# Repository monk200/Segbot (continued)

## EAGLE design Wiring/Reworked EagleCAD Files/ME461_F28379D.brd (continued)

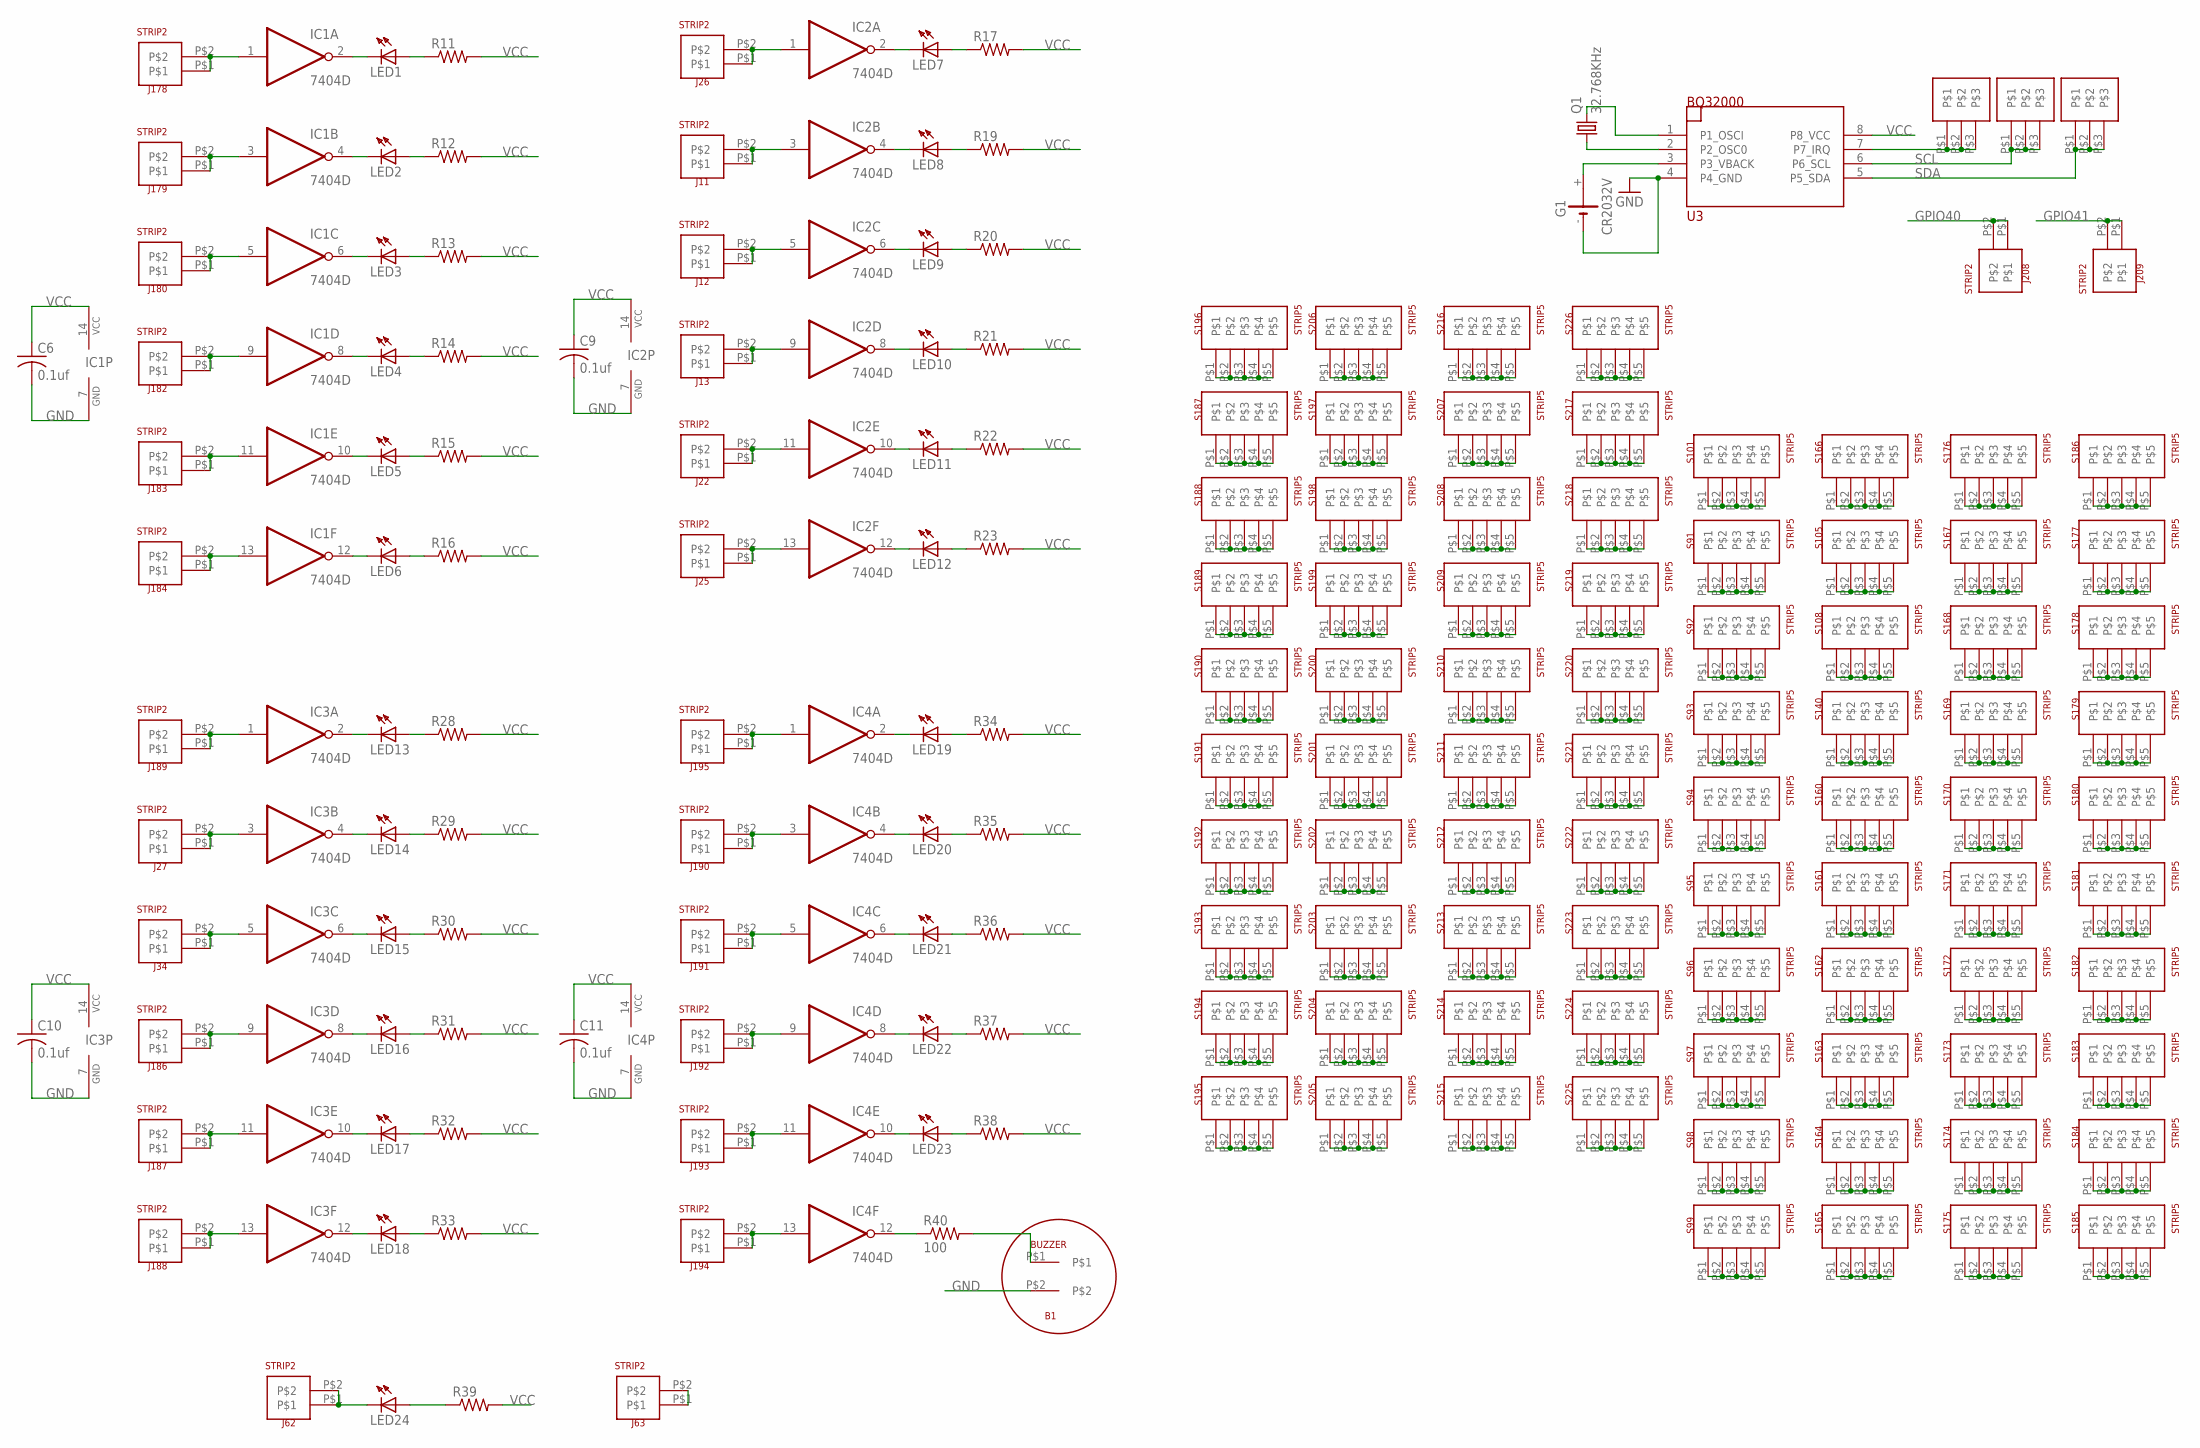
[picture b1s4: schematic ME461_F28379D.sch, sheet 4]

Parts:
B1: BUZZER
C6, C9, C10, C11: 0.1uf; C1206
G1: CR2032V
IC1, IC2, IC3, IC4: 7404D; SO14
J1, J2, J3: STRIP3
J11, J12, J13, J22, J25, J26, J27, J34, J62, J63, J178, J179, J180, J182, J183, J184, J186, J187, J188, J189, J190, J191, J192, J193, J194, J195, J208, J209: STRIP2
LED1, LED2, LED3, LED4, LED5, LED6, LED7, LED8, LED9, LED10, LED11, LED12, LED13, LED14, LED15, LED16, LED17, LED18, LED19, LED20, LED21, LED22, LED23, LED24: LED3MM
Q1: 32.768KHz; TC26H
R11, R12, R13, R14, R15, R16, R17, R19, R20, R21, R22, R23, R28, R29, R30, R31, R32, R33, R34, R35, R36, R37, R38, R39: R-US_R1206; R1206
R40: 100; R1206
S91, S92, S93, S94, S95, S96, S97, S98, S99, S101, S105, S108, S140, S160, S161, S162, S163, S164, S165, S166, S167, S168, S169, S170, S171, S172, S173, S174, S175, S176, S177, S178, S179, S180, S181, S182, S183, S184, S185, S186, S187, S188, S189, S190, S191, S192, S193, S194, S195, S196, S197, S198, S199, S200, S201, S202, S203, S204, S205, S206, S207, S208, S209, S210, S211, S212, S213, S214, S215, S216, S217, S218, S219, S220, S221, S222, S223, S224, S225, S226: STRIP5
U3: BQ32000; SO08

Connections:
GND: B1.P$2, C6.2, C9.2, C10.2, C11.2, G1.-, IC1.7 (GND), IC2.7 (GND), IC3.7 (GND), IC4.7 (GND), U3.4 (P4_GND); also elsewhere on the board
GPIO40: J208.P$1, J208.P$2; also elsewhere on the board
GPIO41: J209.P$1, J209.P$2; also elsewhere on the board
unnamed: J62.P$1, J62.P$2, LED24.K (C)
unnamed: IC4.12 (O), R40.1
unnamed: B1.P$1, R40.2
unnamed: Q1.1, U3.2 (P2_OSC0)
unnamed: J63.P$1, J63.P$2
unnamed: Q1.2, U3.1 (P1_OSCI)
unnamed: J1.P$1, J1.P$2, J1.P$3, U3.7 (P7_IRQ)
unnamed: G1.+, U3.3 (P3_VBACK)
unnamed: IC2.1 (I), J26.P$1, J26.P$2
unnamed: IC2.2 (O), LED7.K (C)
unnamed: LED7.A, R17.1
unnamed: IC2.3 (I), J11.P$1, J11.P$2
unnamed: IC2.4 (O), LED8.K (C)
unnamed: LED8.A, R19.1
unnamed: IC2.5 (I), J12.P$1, J12.P$2
unnamed: IC2.6 (O), LED9.K (C)
unnamed: S91.P$1, S91.P$2, S91.P$3, S91.P$4, S91.P$5
unnamed: S92.P$1, S92.P$2, S92.P$3, S92.P$4, S92.P$5
unnamed: S93.P$1, S93.P$2, S93.P$3, S93.P$4, S93.P$5
unnamed: S94.P$1, S94.P$2, S94.P$3, S94.P$4, S94.P$5
unnamed: S95.P$1, S95.P$2, S95.P$3, S95.P$4, S95.P$5
unnamed: S96.P$1, S96.P$2, S96.P$3, S96.P$4, S96.P$5
unnamed: S97.P$1, S97.P$2, S97.P$3, S97.P$4, S97.P$5
unnamed: S98.P$1, S98.P$2, S98.P$3, S98.P$4, S98.P$5
unnamed: S99.P$1, S99.P$2, S99.P$3, S99.P$4, S99.P$5
unnamed: S101.P$1, S101.P$2, S101.P$3, S101.P$4, S101.P$5
unnamed: S105.P$1, S105.P$2, S105.P$3, S105.P$4, S105.P$5
unnamed: S108.P$1, S108.P$2, S108.P$3, S108.P$4, S108.P$5
unnamed: S140.P$1, S140.P$2, S140.P$3, S140.P$4, S140.P$5
unnamed: S160.P$1, S160.P$2, S160.P$3, S160.P$4, S160.P$5
unnamed: S161.P$1, S161.P$2, S161.P$3, S161.P$4, S161.P$5
unnamed: S162.P$1, S162.P$2, S162.P$3, S162.P$4, S162.P$5
unnamed: S163.P$1, S163.P$2, S163.P$3, S163.P$4, S163.P$5
unnamed: S164.P$1, S164.P$2, S164.P$3, S164.P$4, S164.P$5
unnamed: S165.P$1, S165.P$2, S165.P$3, S165.P$4, S165.P$5
unnamed: S166.P$1, S166.P$2, S166.P$3, S166.P$4, S166.P$5
unnamed: S167.P$1, S167.P$2, S167.P$3, S167.P$4, S167.P$5
unnamed: S168.P$1, S168.P$2, S168.P$3, S168.P$4, S168.P$5
unnamed: S169.P$1, S169.P$2, S169.P$3, S169.P$4, S169.P$5
unnamed: S170.P$1, S170.P$2, S170.P$3, S170.P$4, S170.P$5
unnamed: S171.P$1, S171.P$2, S171.P$3, S171.P$4, S171.P$5
unnamed: S172.P$1, S172.P$2, S172.P$3, S172.P$4, S172.P$5
unnamed: S173.P$1, S173.P$2, S173.P$3, S173.P$4, S173.P$5
unnamed: S174.P$1, S174.P$2, S174.P$3, S174.P$4, S174.P$5
unnamed: S175.P$1, S175.P$2, S175.P$3, S175.P$4, S175.P$5
unnamed: S176.P$1, S176.P$2, S176.P$3, S176.P$4, S176.P$5
unnamed: S177.P$1, S177.P$2, S177.P$3, S177.P$4, S177.P$5
unnamed: S178.P$1, S178.P$2, S178.P$3, S178.P$4, S178.P$5
unnamed: S179.P$1, S179.P$2, S179.P$3, S179.P$4, S179.P$5
unnamed: S180.P$1, S180.P$2, S180.P$3, S180.P$4, S180.P$5
unnamed: S181.P$1, S181.P$2, S181.P$3, S181.P$4, S181.P$5
unnamed: S182.P$1, S182.P$2, S182.P$3, S182.P$4, S182.P$5
unnamed: S183.P$1, S183.P$2, S183.P$3, S183.P$4, S183.P$5
unnamed: S184.P$1, S184.P$2, S184.P$3, S184.P$4, S184.P$5
unnamed: S185.P$1, S185.P$2, S185.P$3, S185.P$4, S185.P$5
unnamed: S186.P$1, S186.P$2, S186.P$3, S186.P$4, S186.P$5
unnamed: S187.P$1, S187.P$2, S187.P$3, S187.P$4, S187.P$5
unnamed: S188.P$1, S188.P$2, S188.P$3, S188.P$4, S188.P$5
unnamed: S189.P$1, S189.P$2, S189.P$3, S189.P$4, S189.P$5
unnamed: S190.P$1, S190.P$2, S190.P$3, S190.P$4, S190.P$5
unnamed: S191.P$1, S191.P$2, S191.P$3, S191.P$4, S191.P$5
unnamed: S192.P$1, S192.P$2, S192.P$3, S192.P$4, S192.P$5
unnamed: S193.P$1, S193.P$2, S193.P$3, S193.P$4, S193.P$5
unnamed: S194.P$1, S194.P$2, S194.P$3, S194.P$4, S194.P$5
unnamed: S195.P$1, S195.P$2, S195.P$3, S195.P$4, S195.P$5
unnamed: S196.P$1, S196.P$2, S196.P$3, S196.P$4, S196.P$5
unnamed: S197.P$1, S197.P$2, S197.P$3, S197.P$4, S197.P$5
unnamed: S198.P$1, S198.P$2, S198.P$3, S198.P$4, S198.P$5
unnamed: S199.P$1, S199.P$2, S199.P$3, S199.P$4, S199.P$5
unnamed: S200.P$1, S200.P$2, S200.P$3, S200.P$4, S200.P$5
unnamed: S201.P$1, S201.P$2, S201.P$3, S201.P$4, S201.P$5
unnamed: S202.P$1, S202.P$2, S202.P$3, S202.P$4, S202.P$5
unnamed: S203.P$1, S203.P$2, S203.P$3, S203.P$4, S203.P$5
unnamed: S204.P$1, S204.P$2, S204.P$3, S204.P$4, S204.P$5
unnamed: S205.P$1, S205.P$2, S205.P$3, S205.P$4, S205.P$5
unnamed: S206.P$1, S206.P$2, S206.P$3, S206.P$4, S206.P$5
unnamed: S207.P$1, S207.P$2, S207.P$3, S207.P$4, S207.P$5
unnamed: S208.P$1, S208.P$2, S208.P$3, S208.P$4, S208.P$5
unnamed: S209.P$1, S209.P$2, S209.P$3, S209.P$4, S209.P$5
unnamed: S210.P$1, S210.P$2, S210.P$3, S210.P$4, S210.P$5
unnamed: S211.P$1, S211.P$2, S211.P$3, S211.P$4, S211.P$5
unnamed: S212.P$1, S212.P$2, S212.P$3, S212.P$4, S212.P$5
unnamed: S213.P$1, S213.P$2, S213.P$3, S213.P$4, S213.P$5
unnamed: S214.P$1, S214.P$2, S214.P$3, S214.P$4, S214.P$5
unnamed: S215.P$1, S215.P$2, S215.P$3, S215.P$4, S215.P$5
unnamed: S216.P$1, S216.P$2, S216.P$3, S216.P$4, S216.P$5
unnamed: S217.P$1, S217.P$2, S217.P$3, S217.P$4, S217.P$5
unnamed: S218.P$1, S218.P$2, S218.P$3, S218.P$4, S218.P$5
unnamed: S219.P$1, S219.P$2, S219.P$3, S219.P$4, S219.P$5
unnamed: S220.P$1, S220.P$2, S220.P$3, S220.P$4, S220.P$5
unnamed: S221.P$1, S221.P$2, S221.P$3, S221.P$4, S221.P$5
unnamed: S222.P$1, S222.P$2, S222.P$3, S222.P$4, S222.P$5
unnamed: S223.P$1, S223.P$2, S223.P$3, S223.P$4, S223.P$5
unnamed: S224.P$1, S224.P$2, S224.P$3, S224.P$4, S224.P$5
unnamed: S225.P$1, S225.P$2, S225.P$3, S225.P$4, S225.P$5
unnamed: S226.P$1, S226.P$2, S226.P$3, S226.P$4, S226.P$5
unnamed: IC1.1 (I), J178.P$1, J178.P$2
unnamed: IC1.2 (O), LED1.K (C)
unnamed: LED1.A, R11.1
unnamed: IC1.3 (I), J179.P$1, J179.P$2
unnamed: IC1.4 (O), LED2.K (C)
unnamed: LED2.A, R12.1
unnamed: IC1.5 (I), J180.P$1, J180.P$2
unnamed: IC1.6 (O), LED3.K (C)
unnamed: LED3.A, R13.1
unnamed: IC1.9 (I), J182.P$1, J182.P$2
unnamed: IC1.8 (O), LED4.K (C)
unnamed: LED4.A, R14.1
unnamed: IC1.11 (I), J183.P$1, J183.P$2
unnamed: IC1.10 (O), LED5.K (C)
unnamed: LED5.A, R15.1
unnamed: IC1.13 (I), J184.P$1, J184.P$2
unnamed: IC1.12 (O), LED6.K (C)
unnamed: LED6.A, R16.1
unnamed: LED9.A, R20.1
unnamed: IC2.9 (I), J13.P$1, J13.P$2
unnamed: IC2.8 (O), LED10.K (C)
unnamed: LED10.A, R21.1
unnamed: IC2.11 (I), J22.P$1, J22.P$2
unnamed: IC2.10 (O), LED11.K (C)
unnamed: LED11.A, R22.1
unnamed: IC2.13 (I), J25.P$1, J25.P$2
unnamed: IC2.12 (O), LED12.K (C)
unnamed: LED12.A, R23.1
unnamed: IC3.1 (I), J189.P$1, J189.P$2
unnamed: IC3.2 (O), LED13.K (C)
unnamed: LED13.A, R28.1
unnamed: IC3.3 (I), J27.P$1, J27.P$2
unnamed: IC3.4 (O), LED14.K (C)
unnamed: LED14.A, R29.1
unnamed: IC3.5 (I), J34.P$1, J34.P$2
unnamed: IC3.6 (O), LED15.K (C)
unnamed: LED15.A, R30.1
unnamed: IC3.9 (I), J186.P$1, J186.P$2
unnamed: IC3.8 (O), LED16.K (C)
unnamed: LED16.A, R31.1
unnamed: IC3.11 (I), J187.P$1, J187.P$2
unnamed: IC3.10 (O), LED17.K (C)
unnamed: LED17.A, R32.1
unnamed: IC3.13 (I), J188.P$1, J188.P$2
unnamed: IC3.12 (O), LED18.K (C)
unnamed: LED18.A, R33.1
unnamed: IC4.1 (I), J195.P$1, J195.P$2
unnamed: IC4.2 (O), LED19.K (C)
unnamed: LED19.A, R34.1
unnamed: IC4.3 (I), J190.P$1, J190.P$2
unnamed: IC4.4 (O), LED20.K (C)
unnamed: LED20.A, R35.1
unnamed: IC4.5 (I), J191.P$1, J191.P$2
unnamed: IC4.6 (O), LED21.K (C)
unnamed: LED21.A, R36.1
unnamed: IC4.9 (I), J192.P$1, J192.P$2
unnamed: IC4.8 (O), LED22.K (C)
unnamed: LED22.A, R37.1
unnamed: IC4.11 (I), J193.P$1, J193.P$2
unnamed: IC4.10 (O), LED23.K (C)
unnamed: LED23.A, R38.1
unnamed: IC4.13 (I), J194.P$1, J194.P$2
unnamed: LED24.A, R39.1
SCL: J2.P$1, J2.P$2, J2.P$3, U3.6 (P6_SCL)
SDA: J3.P$1, J3.P$2, J3.P$3, U3.5 (P5_SDA)
VCC: C6.1, C9.1, C10.1, C11.1, IC1.14 (VCC), IC2.14 (VCC), IC3.14 (VCC), IC4.14 (VCC), R11.2, R12.2, R13.2, R14.2, R15.2, R16.2, R17.2, R19.2, R20.2, R21.2, R22.2, R23.2, R28.2, R29.2, R30.2, R31.2, R32.2, R33.2, R34.2, R35.2, R36.2, R37.2, R38.2, R39.2, U3.8 (P8_VCC); also elsewhere on the board

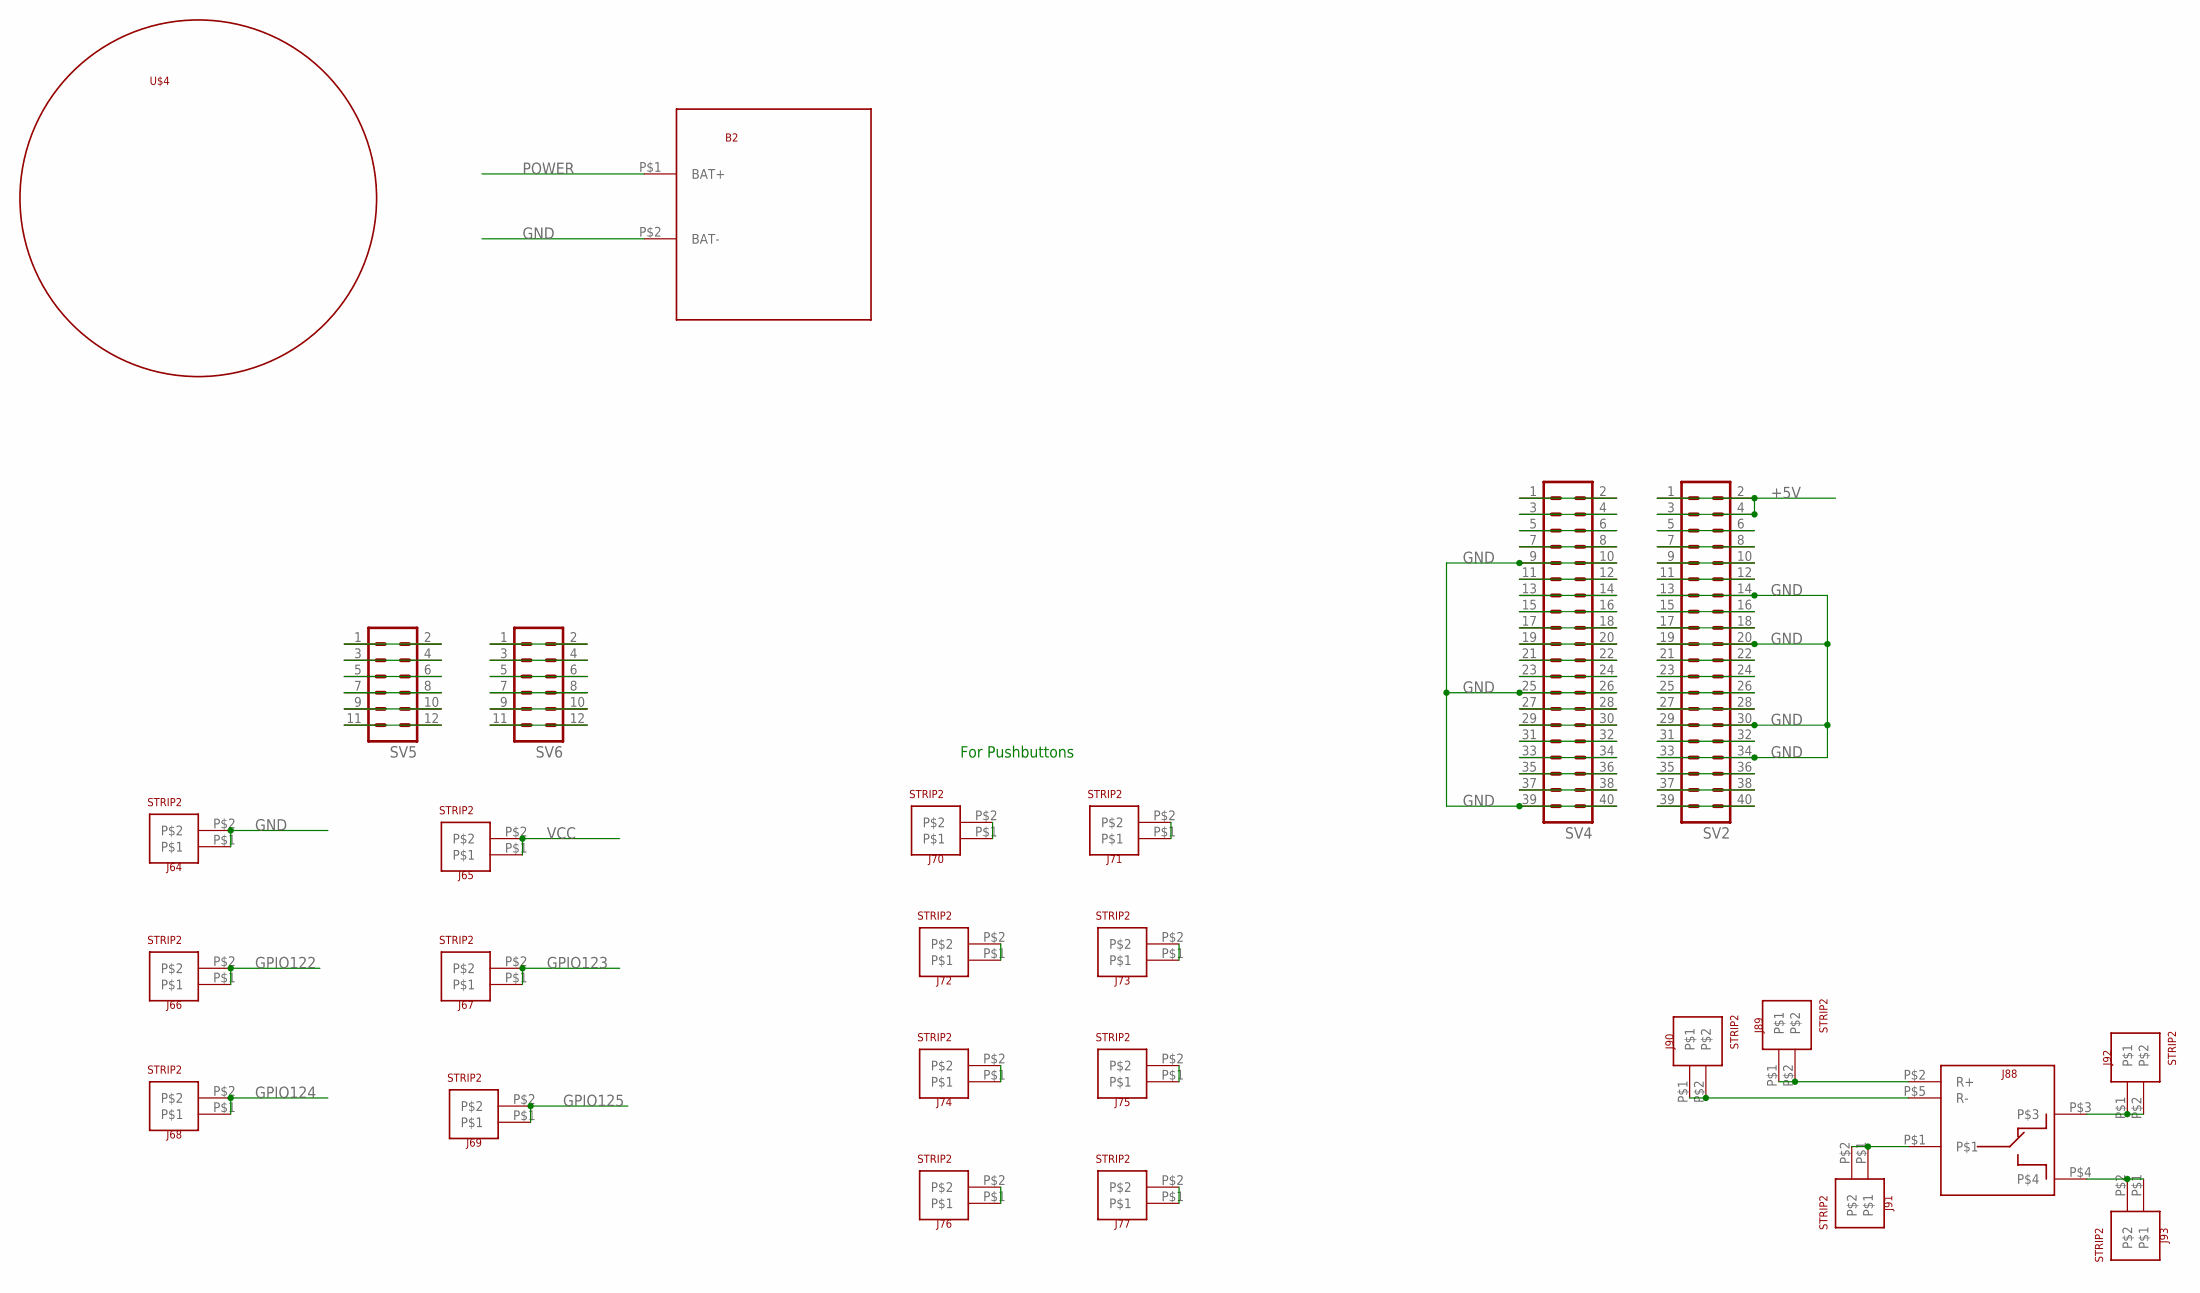
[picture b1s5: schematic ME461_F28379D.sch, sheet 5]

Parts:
B2: BATTERY_4AA_HOLDER
J64, J65, J66, J67, J68, J69, J70, J71, J72, J73, J74, J75, J76, J77, J89, J90, J91, J92, J93: STRIP2
J88: RELAY_JQC-3F_5V
SV2, SV4: MA20-2
SV5, SV6: MA06-2
U$4: CASTERWHEEL

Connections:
+5V: SV2.1, SV2.2, SV2.3, SV2.4; also elsewhere on the board
GND: B2.P$2 (BAT-), J64.P$1, J64.P$2, SV2.13, SV2.14, SV2.19, SV2.20, SV2.29, SV2.30, SV2.33, SV2.34, SV4.9, SV4.10, SV4.25, SV4.26, SV4.39, SV4.40; also elsewhere on the board
GPIO122: J66.P$1, J66.P$2; also elsewhere on the board
GPIO123: J67.P$1, J67.P$2; also elsewhere on the board
GPIO124: J68.P$1, J68.P$2; also elsewhere on the board
GPIO125: J69.P$1, J69.P$2; also elsewhere on the board
unnamed: SV4.1, SV4.2
unnamed: SV5.1, SV5.2
unnamed: SV5.3, SV5.4
unnamed: SV5.5, SV5.6
unnamed: SV4.3, SV4.4
unnamed: SV4.5, SV4.6
unnamed: SV4.7, SV4.8
unnamed: SV5.7, SV5.8
unnamed: SV4.11, SV4.12
unnamed: SV4.13, SV4.14
unnamed: SV4.15, SV4.16
unnamed: SV4.17, SV4.18
unnamed: SV4.19, SV4.20
unnamed: SV4.21, SV4.22
unnamed: SV4.23, SV4.24
unnamed: SV5.9, SV5.10
unnamed: SV4.27, SV4.28
unnamed: SV4.29, SV4.30
unnamed: SV4.31, SV4.32
unnamed: SV4.33, SV4.34
unnamed: SV4.35, SV4.36
unnamed: SV4.37, SV4.38
unnamed: SV5.11, SV5.12
unnamed: SV2.39, SV2.40
unnamed: SV2.37, SV2.38
unnamed: SV2.35, SV2.36
unnamed: SV6.1, SV6.2
unnamed: SV2.31, SV2.32
unnamed: SV6.3, SV6.4
unnamed: SV2.27, SV2.28
unnamed: SV2.25, SV2.26
unnamed: SV2.23, SV2.24
unnamed: SV2.21, SV2.22
unnamed: SV6.5, SV6.6
unnamed: SV2.17, SV2.18
unnamed: SV2.15, SV2.16
unnamed: SV6.7, SV6.8
unnamed: SV2.11, SV2.12
unnamed: SV2.9, SV2.10
unnamed: SV2.7, SV2.8
unnamed: SV2.5, SV2.6
unnamed: SV6.9, SV6.10
unnamed: SV6.11, SV6.12
unnamed: J70.P$1, J70.P$2
unnamed: J71.P$1, J71.P$2
unnamed: J72.P$1, J72.P$2
unnamed: J73.P$1, J73.P$2
unnamed: J74.P$1, J74.P$2
unnamed: J75.P$1, J75.P$2
unnamed: J76.P$1, J76.P$2
unnamed: J77.P$1, J77.P$2
unnamed: J88.P$2 (R+), J89.P$1, J89.P$2
unnamed: J88.P$5 (R-), J90.P$1, J90.P$2
unnamed: J88.P$1, J91.P$1, J91.P$2
unnamed: J88.P$3, J92.P$1, J92.P$2
unnamed: J88.P$4, J93.P$1, J93.P$2
POWER: B2.P$1 (BAT+); also elsewhere on the board
VCC: J65.P$1, J65.P$2; also elsewhere on the board

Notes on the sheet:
For Pushbuttons

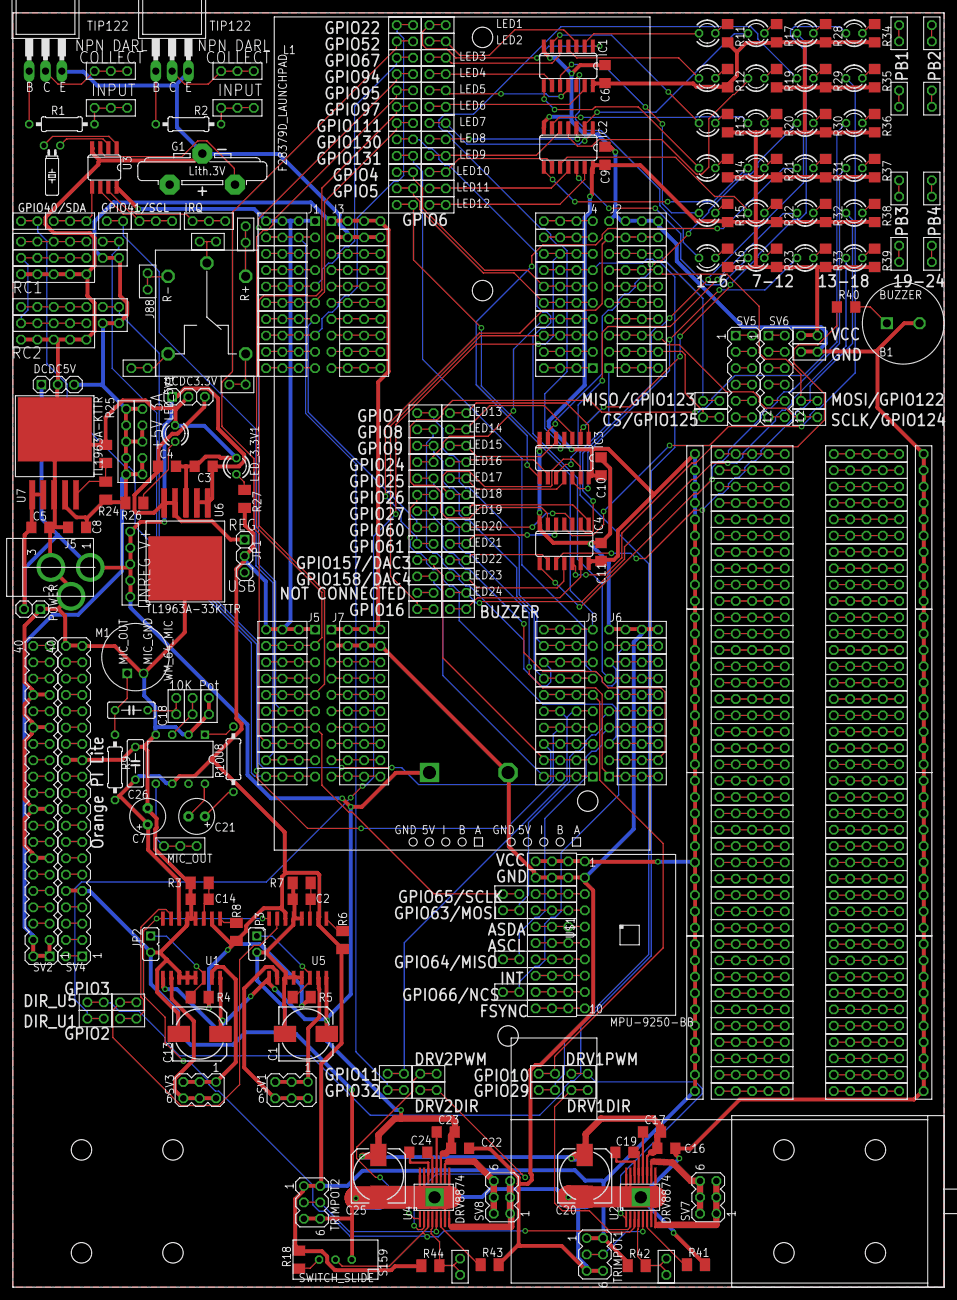
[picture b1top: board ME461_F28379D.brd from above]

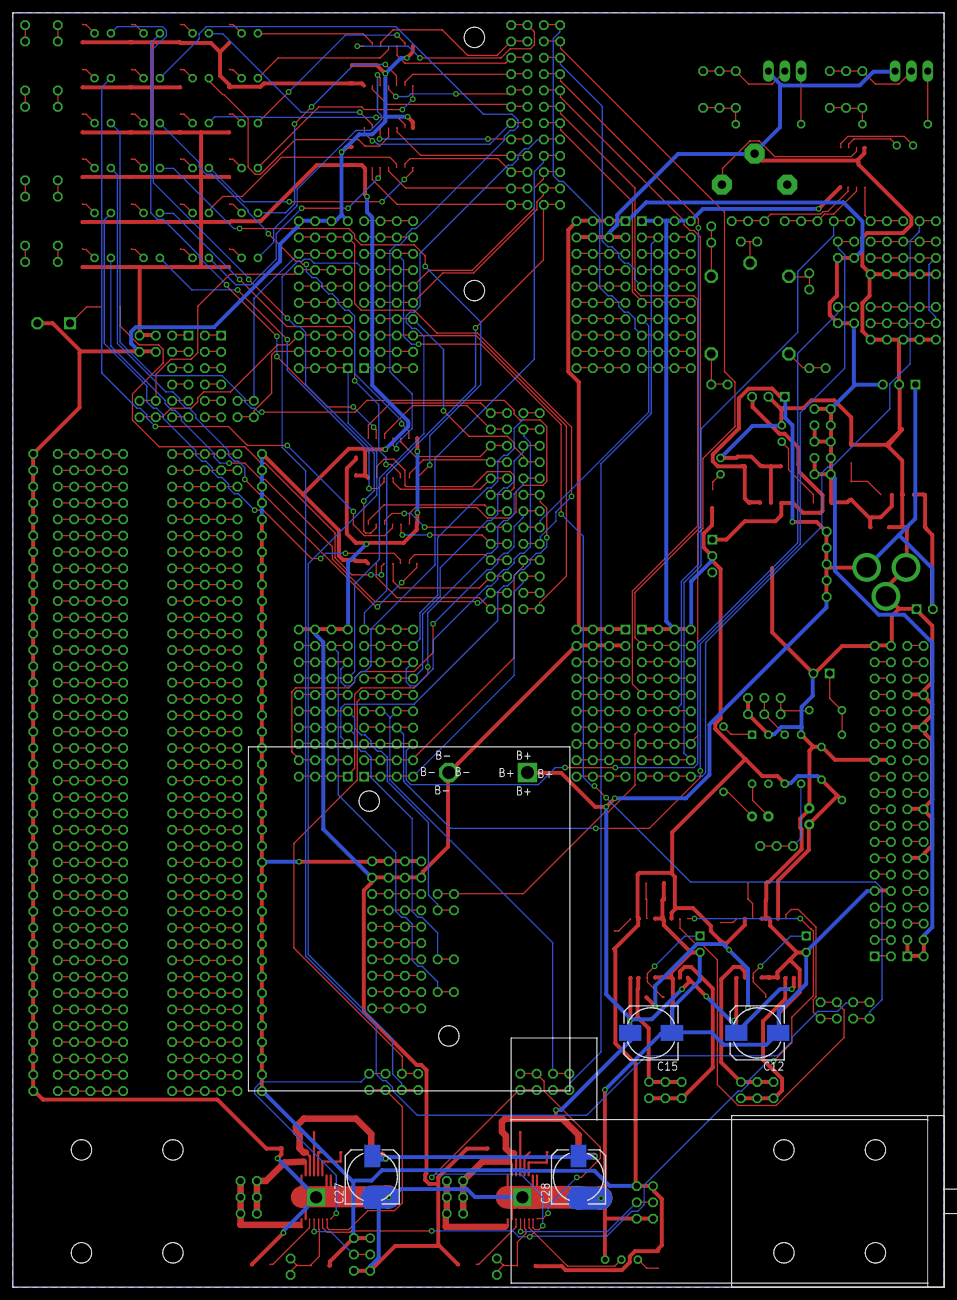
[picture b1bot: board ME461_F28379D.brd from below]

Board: 2 copper layers, 144.8 x 198.1 mm, 432 parts (6 on the bottom side), 355 nets.

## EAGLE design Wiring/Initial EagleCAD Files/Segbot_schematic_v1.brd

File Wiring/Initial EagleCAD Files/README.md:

# PCB for Initial Design
EagleCAD was used to design the circuit board for the initial design. The circuit schematic can be seen to very closely resemble the [initial wiring diagram](https://github.com/monk200/Segbot/blob/main/Wiring/Initial%20Design%20Wiring%20Diagram.png). The board was intened to be fabricated at https://www.4pcb.com/ because students get a discount that their boards only cost $33 and they have their own [free file checker](https://www.4pcb.com/free-pcb-file-check/index.html).  

## Wiring Considerations
I tethered the AD0 pin on the MPU-6050 to ground because it is used to toggle between two slave addresses, which is unneccesary in this case. By tethering it to ground, the slave address is set to 0x68 and one less pin on the MSP-430 needs to be occupied. I also connected PMODE on both DRV8874 chips to ground to select the control mode that takes an enable input and a phase. The capacitors and resistors connected directly to the DRV8874 chips are based on the diagram from [page 9 of the datasheet](https://www.ti.com/lit/ds/symlink/drv8874.pdf?ts=1621215513855&ref_url=https%253A%252F%252Fwww.ti.com%252Fproduct%252FDRV8874). Lastly, since the MPU-6050 is already using UCB for its clock and reading data, the LS73366R chips are using UCA instead of leaving UCA for connecting to a terminal emulator. This is slightly inconvenient for programming and debugging purposees but is a necesssary sacrifice to connect the required circuitry.  

## Custom Parts
The only custom part that I needed to create was the MPU-6050 ([MPU6050_MODULE in SE423EagleLibrary.lbr](https://github.com/monk200/Segbot/blob/main/Wiring/Initial%20EagleCAD%20Files/SE423EagleLibrary.lbr)). The module chosen didn't list the exact information on the pin spacing so some assumptions were made that since it is technically an Arduino module, the pins would be spaced the same distance apart. Other than that, the circuit design was fairly simple to work through.  

## 4PCB File Check
Running my design through the free file checker produced no major issues and it automatically fixed a recurring line width error I made. The specific error message output was "Insufficient Silkscreen Line Width (1543 violations)," and, as I noted, the file checker automatically fixed the error.  

## EagleCAD Design

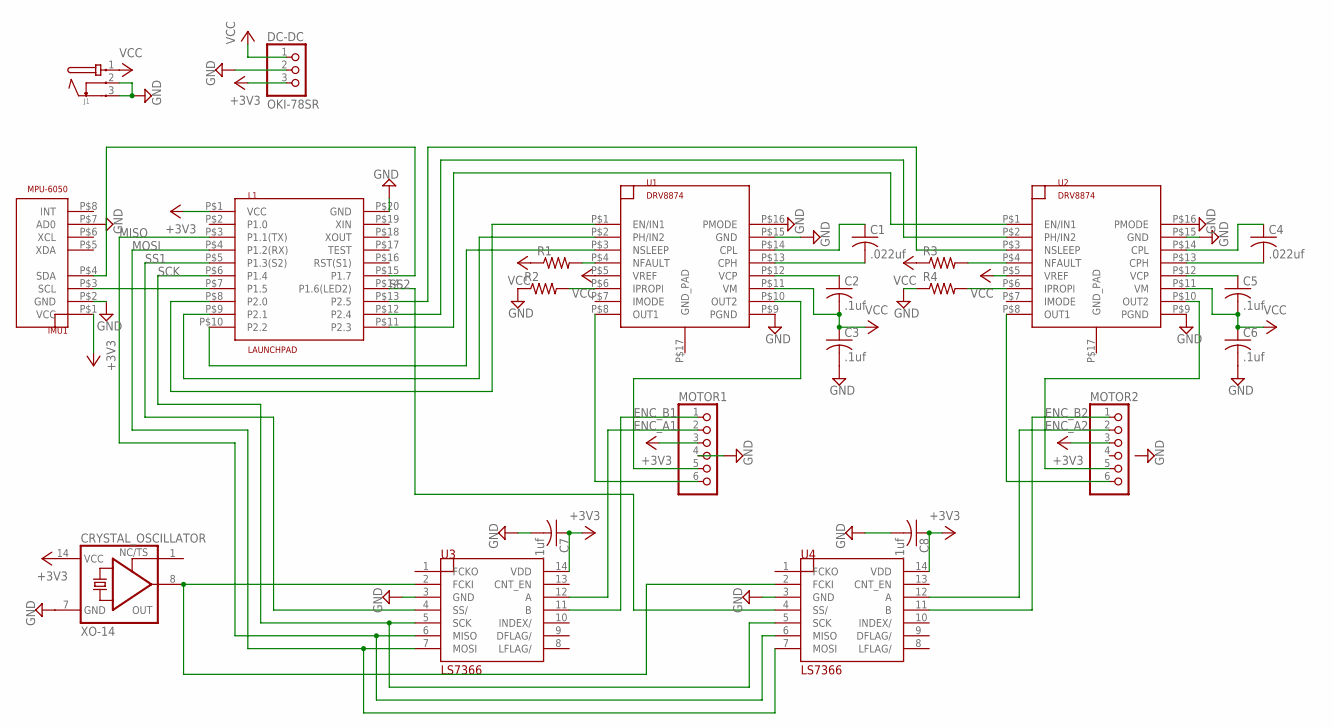
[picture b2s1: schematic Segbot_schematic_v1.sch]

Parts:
C1, C4: .022uf; C025-024X044
C2, C3, C5, C6: .1uf; C025-024X044
C7, C8: .1uf; C1206
CRYSTAL_OSCILLATOR: XO-14; DIL14S
DC-DC: OKI-78SR; 1X03
IMU1: MPU-6050; MPU6050_MODULE
J1: JACK-PMS
L1: LAUNCHPAD
MOTOR1, MOTOR2: PINHD-1X6; 1X06
R1, R2, R3, R4: R-US_R1206; R1206
U1, U2: DRV8874; HTSSOP16
U3, U4: LS7366; SO14

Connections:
+3V3: C7.1, C8.1, CRYSTAL_OSCILLATOR.14 (VCC), DC-DC.3, IMU1.P$1 (VCC), L1.P$1 (VCC), MOTOR1.3, MOTOR2.3, U3.14 (VDD), U4.14 (VDD)
ENC_A1: MOTOR1.2, U3.12 (A)
ENC_A2: MOTOR2.2, U4.12 (A)
ENC_B1: MOTOR1.1, U3.11 (B)
ENC_B2: MOTOR2.1, U4.11 (B)
GND: C3.2, C6.2, C7.2, C8.2, CRYSTAL_OSCILLATOR.7 (GND), DC-DC.2, IMU1.P$2 (GND), IMU1.P$7 (AD0), J1.2, J1.3, L1.P$20 (GND), MOTOR1.4, R2.1, R4.1, U1.P$9 (PGND), U1.P$15 (GND), U1.P$16 (PMODE), U2.P$9 (PGND), U2.P$15 (GND), U2.P$16 (PMODE), U3.3 (GND), U4.3 (GND)
MISO: L1.P$3 (P1.1(TX)), U3.6 (MISO), U4.6 (MISO)
MOSI: L1.P$4 (P1.2(RX)), U3.7 (MOSI), U4.7 (MOSI)
unnamed: IMU1.P$3 (SCL), L1.P$7 (P1.5)
unnamed: IMU1.P$4 (SDA), L1.P$15 (P1.7)
unnamed: L1.P$8 (P2.0), U1.P$1 (EN/IN1)
unnamed: L1.P$9 (P2.1), U1.P$2 (PH/IN2)
unnamed: L1.P$10 (P2.2), U1.P$3 (NSLEEP)
unnamed: R1.2, U1.P$4 (NFAULT)
unnamed: R2.2, U1.P$6 (IPROPI)
unnamed: C1.1, U1.P$14 (CPL)
unnamed: C1.2, U1.P$13 (CPH)
unnamed: C2.1, U1.P$12 (VCP)
unnamed: MOTOR1.6, U1.P$8 (OUT1)
unnamed: MOTOR1.5, U1.P$10 (OUT2)
unnamed: L1.P$11 (P2.3), U2.P$1 (EN/IN1)
unnamed: L1.P$12 (P2.4), U2.P$2 (PH/IN2)
unnamed: L1.P$13 (P2.5), U2.P$3 (NSLEEP)
unnamed: C4.1, U2.P$14 (CPL)
unnamed: C4.2, U2.P$13 (CPH)
unnamed: C5.1, U2.P$12 (VCP)
unnamed: R3.2, U2.P$4 (NFAULT)
unnamed: R4.2, U2.P$6 (IPROPI)
unnamed: MOTOR2.6, U2.P$8 (OUT1)
unnamed: MOTOR2.5, U2.P$10 (OUT2)
unnamed: CRYSTAL_OSCILLATOR.8 (OUT), U3.2 (FCKI), U4.2 (FCKI)
SCK: L1.P$6 (P1.4), U3.5 (SCK), U4.5 (SCK)
SS1: L1.P$5 (P1.3(S2)), U3.4 (SS/)
SS2: L1.P$14 (P1.6(LED2)), U4.4 (SS/)
VCC: C2.2, C3.1, C5.2, C6.1, DC-DC.1, J1.1, R1.1, R3.1, U1.P$5 (VREF), U1.P$11 (VM), U2.P$5 (VREF), U2.P$11 (VM)
